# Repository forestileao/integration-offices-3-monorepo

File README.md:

# Plant Monitoring System

This document can be better visualized in the GitHub repository: https://github.com/forestileao/integration-offices-3-monorepo/blob/main/README.md

In the source code of the project, it is possible to find the following folders:
- api: Contains the backend of the project, built with FastAPI.
- webapp: Contains the frontend of the project, built with Next.js.
- eletronic-design: Contains the eletronic design of the project, built with Kicad.
- firmware: Contains the firmware of the project, built for Raspberry pi 3.
- leaf-detection: python notebooks with the leaf detection algorithm.
- mecanic-design: AutoCAD files with the mecanic design of the project.
- arduino-codes: Testing codes for the Arduino (Used for testing the components)

Source Code link: https://github.com/forestileao/integration-offices-3-monorepo

This project is a Plant Monitoring System built with FastAPI for the backend and Next.js for the frontend.

## Table of Contents

- [Prerequisites](#prerequisites)
- [Setup](#setup)
- [Running the Project](#running-the-project)
- [Project Structure](#project-structure)
- [API Endpoints](#api-endpoints)
- [Learn More](#learn-more)

## Prerequisites

- Python 3.8+
- Node.js 14+
- npm or yarn

## Setup

### Backend

1. Clone the repository:

   ```sh
   git clone <repository-url>
   cd <repository-directory>/api
   ```

2. Create a virtual environment and activate it:

   ```sh
   python -m venv venv
   source venv/bin/activate  # On Windows use `venv\Scripts\activate`
   ```

3. Install the dependencies:

   ```sh
   pip install -r requirements.txt
   ```

4. Initialize the database:

   ```sh
   python -c "from app import initialize_database; initialize_database()"
   ```

### Frontend

1. Navigate to the `webapp` directory:

   ```sh
   cd ../webapp
   ```

2. Install the dependencies:

   ```sh
   npm install
   # or
   yarn install
   ```

## Running the Project

### Backend

1. Start the FastAPI server:

   ```sh
   uvicorn app:app --reload
   ```

   The backend server will be running at [http://localhost:8000](http://localhost:8000).

### Frontend

1. Start the Next.js development server:

   ```sh
   npm run dev
   # or
   yarn dev
   ```

   The frontend server will be running at [http://localhost:3000](http://localhost:3000).

## Project Structure

### Backend

- `api/app.py`: Main FastAPI application file containing models, routes, and utility functions.
- `api/database.sql`: SQL script to initialize the database schema.

### Frontend

- `webapp/app/add-user/page.tsx`: Page for adding a new user.
- `webapp/app/create-account/page.tsx`: Page for creating a new account.
- `webapp/components/ui`: UI components used in the frontend.
- `webapp/hooks`: Custom hooks used in the frontend.
- `webapp/api`: API functions to interact with the backend.

## API Endpoints

- `POST /projects/`: Create a new project.
- `GET /projects/`: List all projects.
- `POST /token`: Obtain a JWT token.
- `POST /users/`: Create a new user.
... and more

## Learn More

To learn more about the technologies used in this project, take a look at the following resources:

- [FastAPI Documentation](https://fastapi.tiangolo.com/)
- [Next.js Documentation](https://nextjs.org/docs)
- [SQLAlchemy Documentation](https://docs.sqlalchemy.org/)
- [React Documentation](https://reactjs.org/docs/getting-started.html)

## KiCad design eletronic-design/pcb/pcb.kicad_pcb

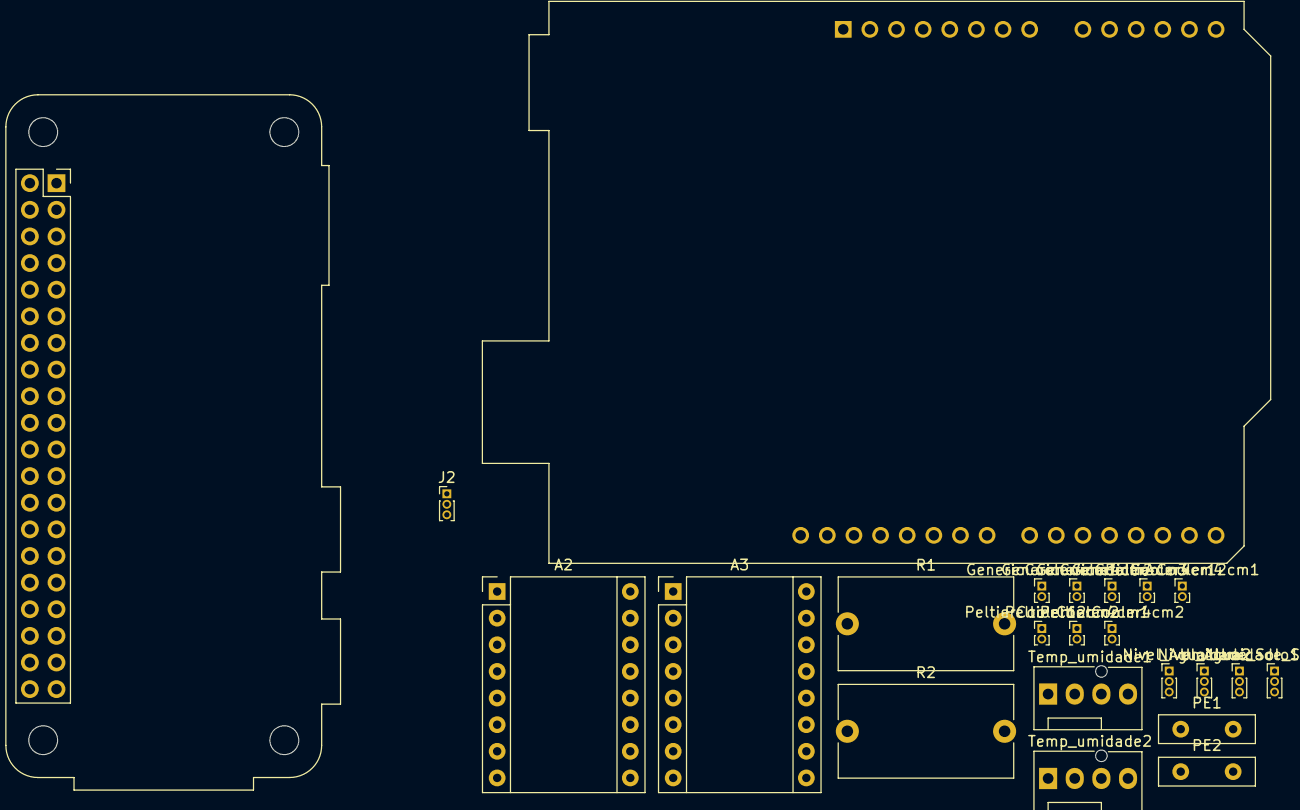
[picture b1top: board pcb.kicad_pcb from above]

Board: 2 copper layers, 23 parts (0 on the bottom side), 3 nets, no tracks yet.

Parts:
A1: Arduino_UNO_R2
A2, A3: Pololu_Breakout_A4988; Pololu_Breakout-16_15.2x20.3mm
GenericCooler4cm1, GenericCooler4cm2, GenericCooler4cm3, GenericCooler4cm4: Conn_01x02_Pin; PinHeader_1x02_P1.00mm_Vertical
J1: Raspberry_Pi_2_3; Raspberry_Pi_Zero_Socketed_THT_FaceDown_MountingHoles
J2: Conn_01x03_Pin; PinHeader_1x03_P1.00mm_Vertical
Nivel_Agua1, Nivel_Agua2: Conn_01x03_Pin; PinHeader_1x03_P1.00mm_Vertical
PE1, PE2: PeltierElement; C_Disc_D9.0mm_W2.5mm_P5.00mm
PeltierCooler4cm1, PeltierCooler4cm2, PeltierCooler12cm1, PeltierCooler12cm2: Conn_01x02_Pin; PinHeader_1x02_P1.00mm_Vertical
R1, R2: Heater; C_Rect_L16.5mm_W8.7mm_P15.00mm_MKT
Temp_umidade1, Temp_umidade2: Conn_01x04; FanPinHeader_1x04_P2.54mm_Vertical
Umidade_Solo1, Umidade_Solo2: Conn_01x03_Pin; PinHeader_1x03_P1.00mm_Vertical

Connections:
unnamed: J1.1 (3V3), J1.17 (3V3)
unnamed: J1.2 (5V), J1.4 (5V)
unnamed: J1.6 (GND), J1.9 (GND), J1.14 (GND), J1.20 (GND), J1.25 (GND), J1.30 (GND), J1.34 (GND), J1.39 (GND)

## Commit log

2024-11-20 init repo
2024-11-20 feat : change folder hierarchy
2024-11-20 fix : limit circuit
2024-11-24 created webapp
2024-11-24 create main pages
2024-11-24 change page name
2024-11-24 feature: create api
2024-11-24 add dockerfile
2024-11-24 refactor
2024-11-24 add auth
2024-11-24 created user login and register
2024-11-24 integrated login and password
2024-11-24 created roles and projects aassignments
2024-11-24 fix lint
2024-11-25 added charts
2024-11-25 added api_url
2024-11-25 fix build
2024-11-25 add env copnfig
2024-11-25 add next public api url
2024-11-25 add public env
2024-11-26 feature: add delete and list projects integration
2024-11-26 feature: add public url
2024-11-26 add postgres
2024-11-26 test
2024-11-26 aaaa
2024-11-26 fixed pydantic version
2024-11-26 docker build
2024-11-26 asdasdsa
2024-11-26 fix sql
2024-11-27 feature: add watershed for leaf count
2024-11-27 made a lot of things :D
2024-11-27 asdasda
2024-11-28 set viewer as disabled
2024-11-28 estimates
2024-11-28 pastel
2024-12-02 codigos de teste do arduino
2024-12-04 add get cahmber parameters
2024-12-04 feature: add firmware
2024-12-07 feature: add firmware flow
2024-12-07 feature: chaged pkg anmes
2024-12-07 import datetime
2024-12-08 waterlevel
2024-12-08 add async session
2024-12-08 update minutes
2024-12-08 update postgres driver
2024-12-08 asdasdasd
2024-12-08 asdasd
2024-12-08 nice
2024-12-08 fixed slash
2024-12-08 fix watershed in api
2024-12-08 fix file read
2024-12-08 fix images
2024-12-08 fix image upload
2024-12-08 stepper motors working
2024-12-08 fix: delete project
2024-12-08 feature: add white control when taking photo
2024-12-08 add water level
2024-12-08 add soil and water level proportion
2024-12-14 add multiplexer code
2024-12-14 feature: add fans controller
2024-12-14 add test for http api
2024-12-14 fix circular import
2024-12-14 abelha
2024-12-14 added print
2024-12-14 added delay
2024-12-14 added read retry
2024-12-14 added setup retry
2024-12-15 set peltier pin
2024-12-15 add test
2024-12-15 set turn on peltier
2024-12-15 deactivate stepper
2024-12-15 add multiplexer
2024-12-15 add pwm pins
2024-12-15 remove multiplexrt
2024-12-16 it works
2024-12-17 readd watershed
2024-12-17 add volume
2024-12-17 feat(pump) : add pump demo feat(fans) : add fans demo (not working 100%)
2024-12-18 add data refresher
2024-12-18 firmware changes
2024-12-18 fix decimal cases
2024-12-18 increase sealy
2024-12-19 update green mask
2024-12-19 adsasd
2024-12-19 add multi
2024-12-19 update photo function and comments on main
2024-12-19 cahgne chamber location
2024-12-19 change ip
2024-12-19 add charts
2025-01-07 add: mecanic design
2025-01-09 fixed docker chamber ids
2025-01-09 set multiplexer
2025-01-09 fix control soil moisture
2025-01-13 coisa boa
2025-01-14 update api
2025-01-14 firmware depressao
2025-01-16 asdsada
2025-01-17 fix fans
2025-01-17 aaaaaeee caralho
2025-01-19 external Fan pin
2025-01-20 finish
2025-01-20 externalFan
2025-01-20 uncomment features
2025-01-23 set temperature range to turn off both
2025-01-23 set pastel
2025-01-23 config variables
2025-01-26 fixed
2025-01-26 add irrigation timer
2025-01-27 set correct soild moisture irrigation
2025-01-27 put correct green are proportion
2025-01-31 firmware
2025-01-31 use const
2025-02-02 hgfh
2025-02-02 asdas
2025-02-02 ffix saporra
2025-02-26 Add README
